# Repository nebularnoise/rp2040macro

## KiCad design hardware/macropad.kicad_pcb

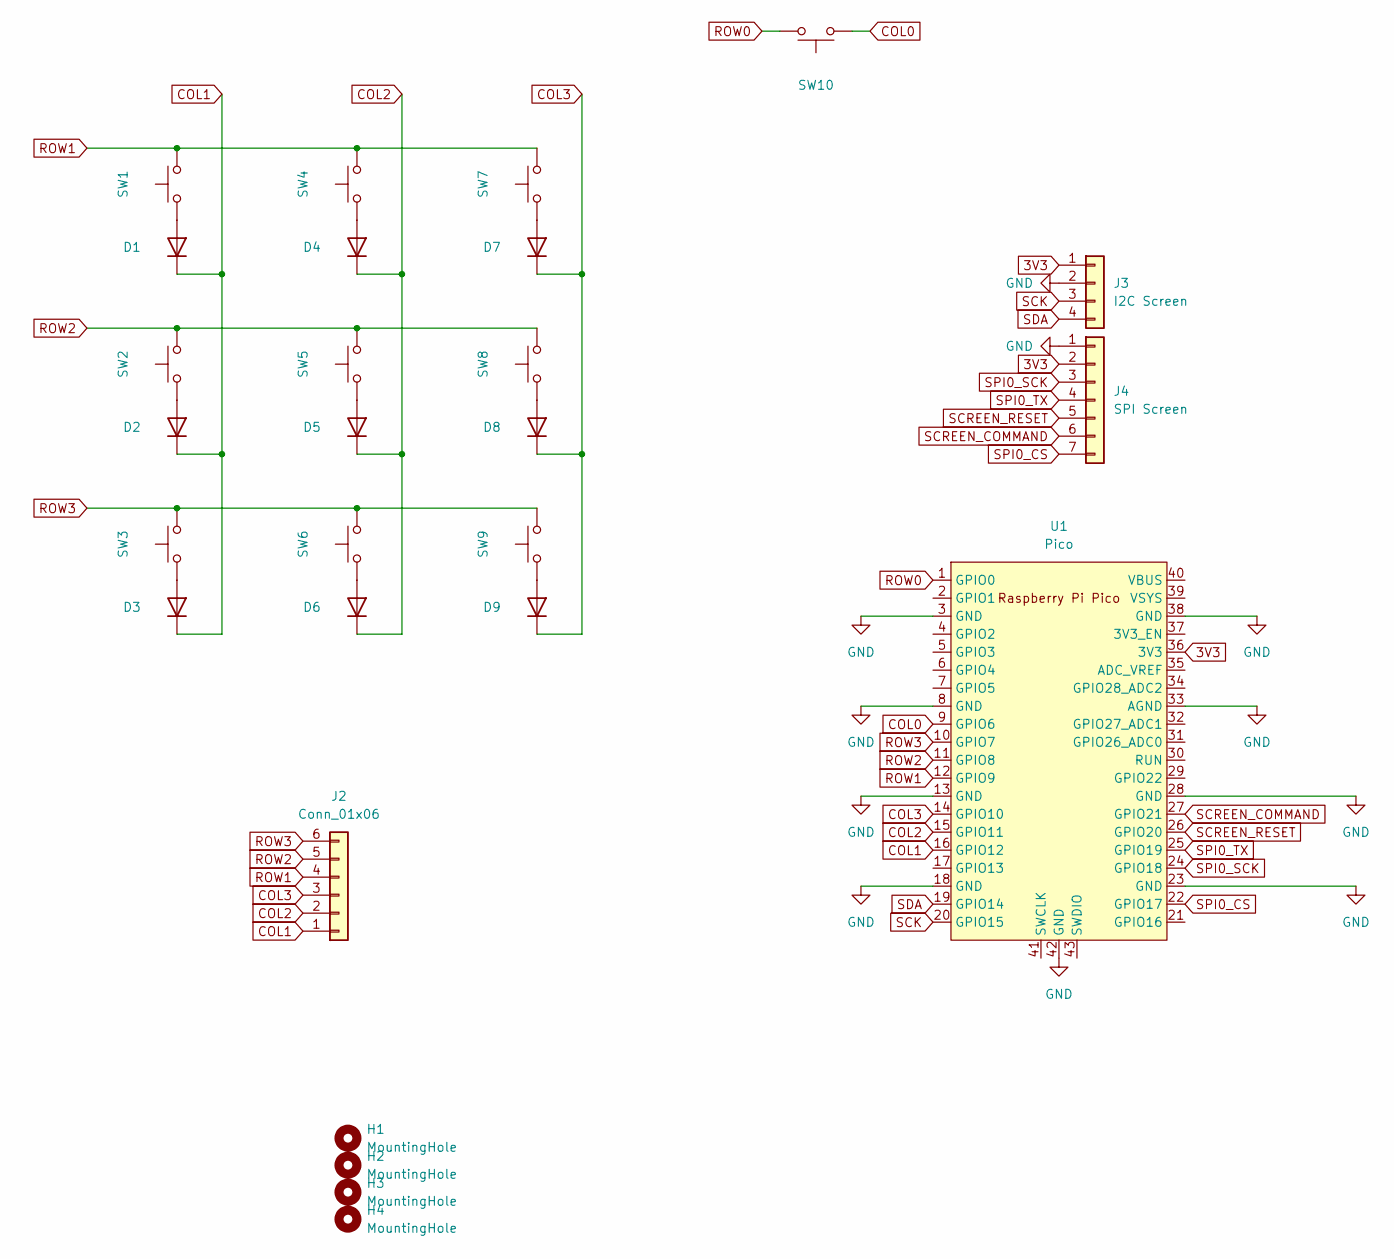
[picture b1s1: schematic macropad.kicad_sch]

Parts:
D1, D2, D3, D4, D5, D6, D7, D8, D9: D; D_DO-41_SOD81_P10.16mm_Horizontal
H1, H2, H3, H4: MountingHole; MountingHole_3.2mm_M3
J2: Conn_01x06; PinHeader_1x06_P2.54mm_Vertical
J3: I2C Screen; I2C_1.3inch_OLED
J4: SPI Screen; SPI_1.3inch_OLED
SW1, SW2, SW3, SW4, SW5, SW6, SW7, SW8, SW9, SW10: SW_Push; SW_Hotswap_Kailh_MX
U1: Pico; RPi_Pico_SMD_TH

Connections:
3V3: J3.1, J4.2, U1.36 (3V3)
COL0: SW10.2, U1.9 (GPIO6)
COL1: D1.1 (K), D2.1 (K), D3.1 (K), J2.1, U1.16 (GPIO12)
COL2: D4.1 (K), D5.1 (K), D6.1 (K), J2.2, U1.15 (GPIO11)
COL3: D7.1 (K), D8.1 (K), D9.1 (K), J2.3, U1.14 (GPIO10)
GND: J3.2, J4.1, U1.3 (GND), U1.8 (GND), U1.13 (GND), U1.18 (GND), U1.23 (GND), U1.28 (GND), U1.33 (AGND), U1.38 (GND), U1.42 (GND)
unnamed: D1.2 (A), SW1.2
unnamed: D2.2 (A), SW2.2
unnamed: D3.2 (A), SW3.2
unnamed: D4.2 (A), SW4.2
unnamed: D5.2 (A), SW5.2
unnamed: D6.2 (A), SW6.2
unnamed: D7.2 (A), SW7.2
unnamed: D8.2 (A), SW8.2
unnamed: D9.2 (A), SW9.2
ROW0: SW10.1, U1.1 (GPIO0)
ROW1: J2.4, SW1.1, SW4.1, SW7.1, U1.12 (GPIO9)
ROW2: J2.5, SW2.1, SW5.1, SW8.1, U1.11 (GPIO8)
ROW3: J2.6, SW3.1, SW6.1, SW9.1, U1.10 (GPIO7)
SCK: J3.3, U1.20 (GPIO15)
SCREEN_COMMAND: J4.6, U1.27 (GPIO21)
SCREEN_RESET: J4.5, U1.26 (GPIO20)
SDA: J3.4, U1.19 (GPIO14)
SPI0_CS: J4.7, U1.22 (GPIO17)
SPI0_SCK: J4.3, U1.24 (GPIO18)
SPI0_TX: J4.4, U1.25 (GPIO19)

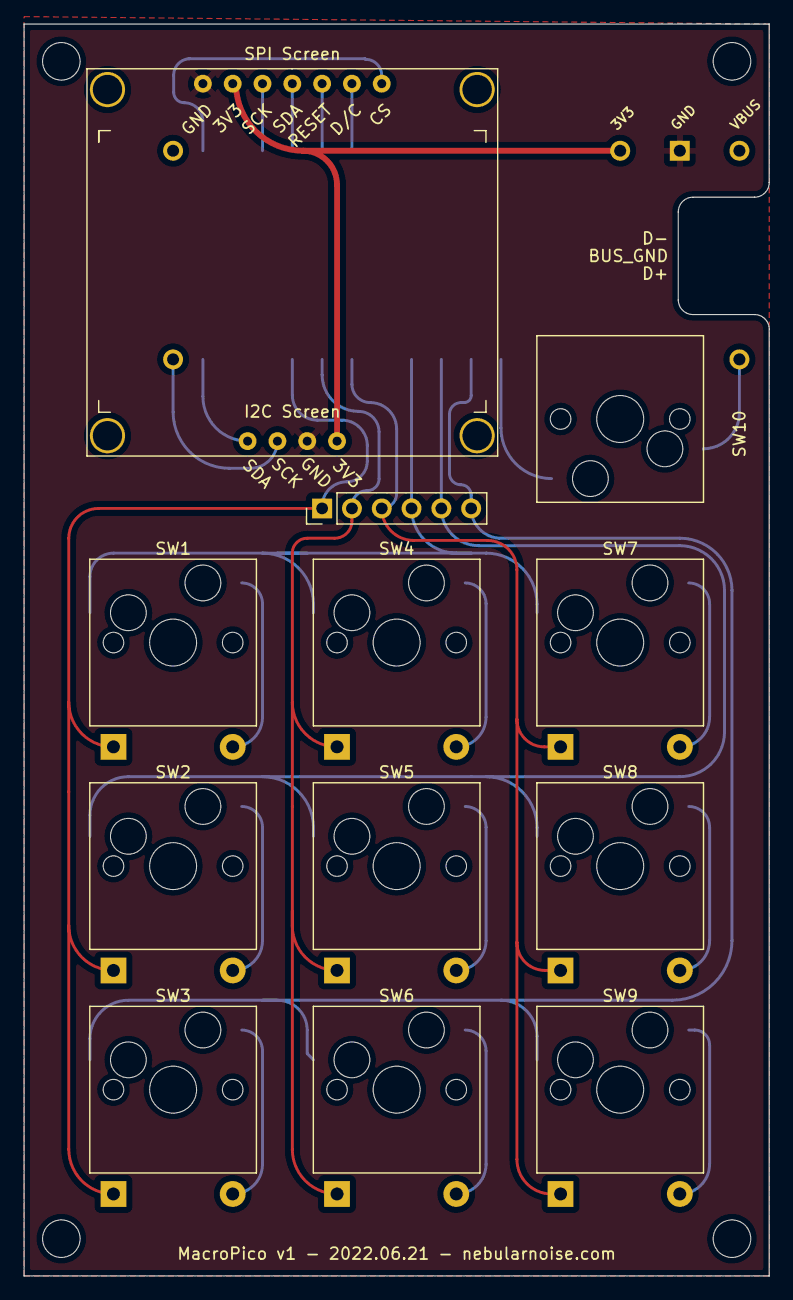
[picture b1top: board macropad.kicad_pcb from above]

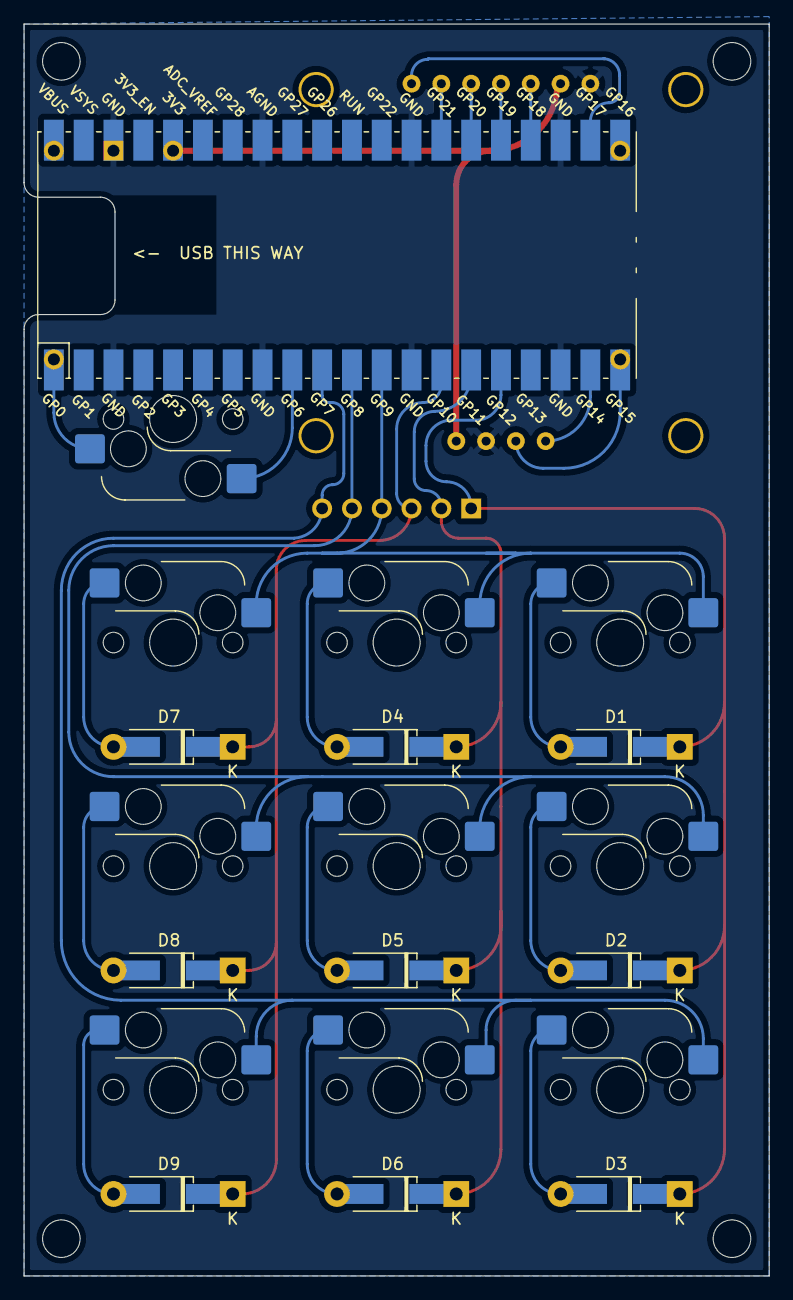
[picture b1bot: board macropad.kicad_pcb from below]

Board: 2 copper layers, 63.5 x 106.7 mm, 27 parts (10 on the bottom side), 26 nets.

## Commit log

2022-06-06 :tada: Init
2022-06-08 :sparkles: Add pico & screen
2022-06-09 :sparkles: Add firmware first draft
    same
    same
2022-06-09 :construction: Add headers for SPI screen also
2022-06-10 :sparkles: Add measurements
2022-06-10 :construction: first draft 3d models
2022-06-10 same
2022-06-13 :truck: Test different layout with pi pico in the back
2022-06-13 :construction: Some routing
2022-06-14 :construction: Edit pi pico to remove tht pads & add castellated pads for D+/D-
2022-06-14 :truck: Move screen headers, before changing footprint
2022-06-14 :construction: Change OLED footprint, reroute to accomodate. Delete USB pads, leave hole instead
2022-06-15 :construction: Move dimensions to user1 layer & adjust base model for easier drawing
2022-06-15 :construction: First draft front panel
2022-06-16 :construction: Add dimension & lock holes
2022-06-16 :construction: Revise models
2022-06-16 :sparkles: Much better parametric model for enclosure
2022-06-16 :construction: Integrate pico 3d model into project
2022-06-16 :construction: Add columns to enclosure
2022-06-17 :construction: update 3d model -- get rid of assembly model
    same
2022-06-21 :truck: move front panel to separate files
2022-06-21 :construction: update model
2022-07-01 :sparkles: add screws to model
2022-07-06 :sparkles: Add rubber feet recesses
2022-07-06 :construction: add support between pcb & front panel
2022-07-07 :bug: Increase clearance
2022-07-07 :bug: Remove ledge around pi pico
2022-07-07 :sparkles: Adapt firmware to new board
2022-07-07 :bug: Fix garbage pixels
2022-07-09 :sparkles: Add usb c variant of 3d model
2022-07-10 :zap: Prefer STEP models
2022-07-10 :zap: Use these models in freecad entire model
    same
2022-07-10 :sparkles: improve usbc module model
2022-07-17 :bug: Fix usb Micro B spacing
